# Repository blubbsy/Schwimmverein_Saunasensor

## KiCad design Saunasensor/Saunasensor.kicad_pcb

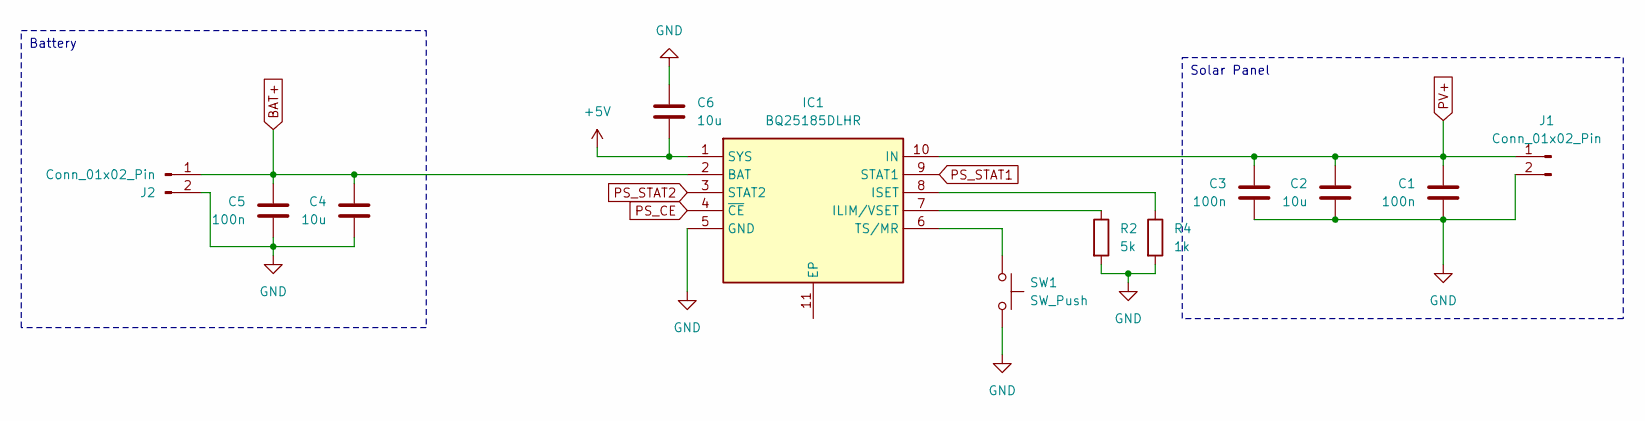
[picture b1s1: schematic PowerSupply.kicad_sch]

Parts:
C1, C3, C5: 100n; C_0805_2012Metric
C2, C4, C6: 10u; C_0805_2012Metric
IC1: BQ25185DLHR; SON40P220X200X80-11N; Mouser Part Number 595-BQ25185DLHR
J1, J2: Conn_01x02_Pin
R2: 5k; R_0805_2012Metric
R4: 1k; R_0805_2012Metric
SW1: SW_Push; SW_Push_1P1T_NO_CK_PTS125Sx43PSMTR

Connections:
+5V: C6.2, IC1.1 (SYS); also elsewhere on the board
BAT+: C4.1, C5.1, IC1.2 (BAT), J2.1; also elsewhere on the board
GND: C1.2, C2.2, C3.2, C4.2, C5.2, C6.1, IC1.5 (GND), J1.2, J2.2, R2.2, R4.2, SW1.2; also elsewhere on the board
unnamed: IC1.7 (ILIM/VSET), R2.1
unnamed: IC1.8 (ISET), R4.1
unnamed: IC1.6 (TS/MR), SW1.1
PS_CE: IC1.4 (~CE); also elsewhere on the board
PS_STAT1: IC1.9 (STAT1); also elsewhere on the board
PS_STAT2: IC1.3 (STAT2); also elsewhere on the board
PV+: C1.1, C2.1, C3.1, IC1.10 (IN), J1.1; also elsewhere on the board

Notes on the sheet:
Solar Panel
Battery

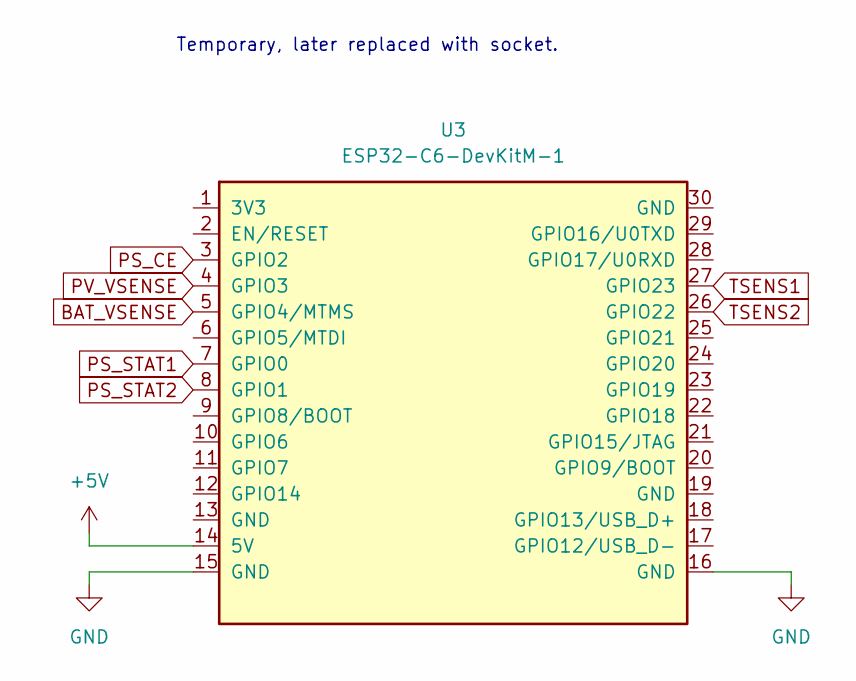
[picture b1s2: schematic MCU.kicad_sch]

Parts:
U3: ESP32-C6-DevKitM-1

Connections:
+5V: U3.14 (5V); also elsewhere on the board
BAT_VSENSE: U3.5 (GPIO4/MTMS); also elsewhere on the board
GND: U3.15 (GND), U3.16 (GND); also elsewhere on the board
PS_CE: U3.3 (GPIO2); also elsewhere on the board
PS_STAT1: U3.7 (GPIO0); also elsewhere on the board
PS_STAT2: U3.8 (GPIO1); also elsewhere on the board
PV_VSENSE: U3.4 (GPIO3); also elsewhere on the board
TSENS1: U3.27 (GPIO23); also elsewhere on the board
TSENS2: U3.26 (GPIO22); also elsewhere on the board

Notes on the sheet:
Temporary, later replaced with socket.

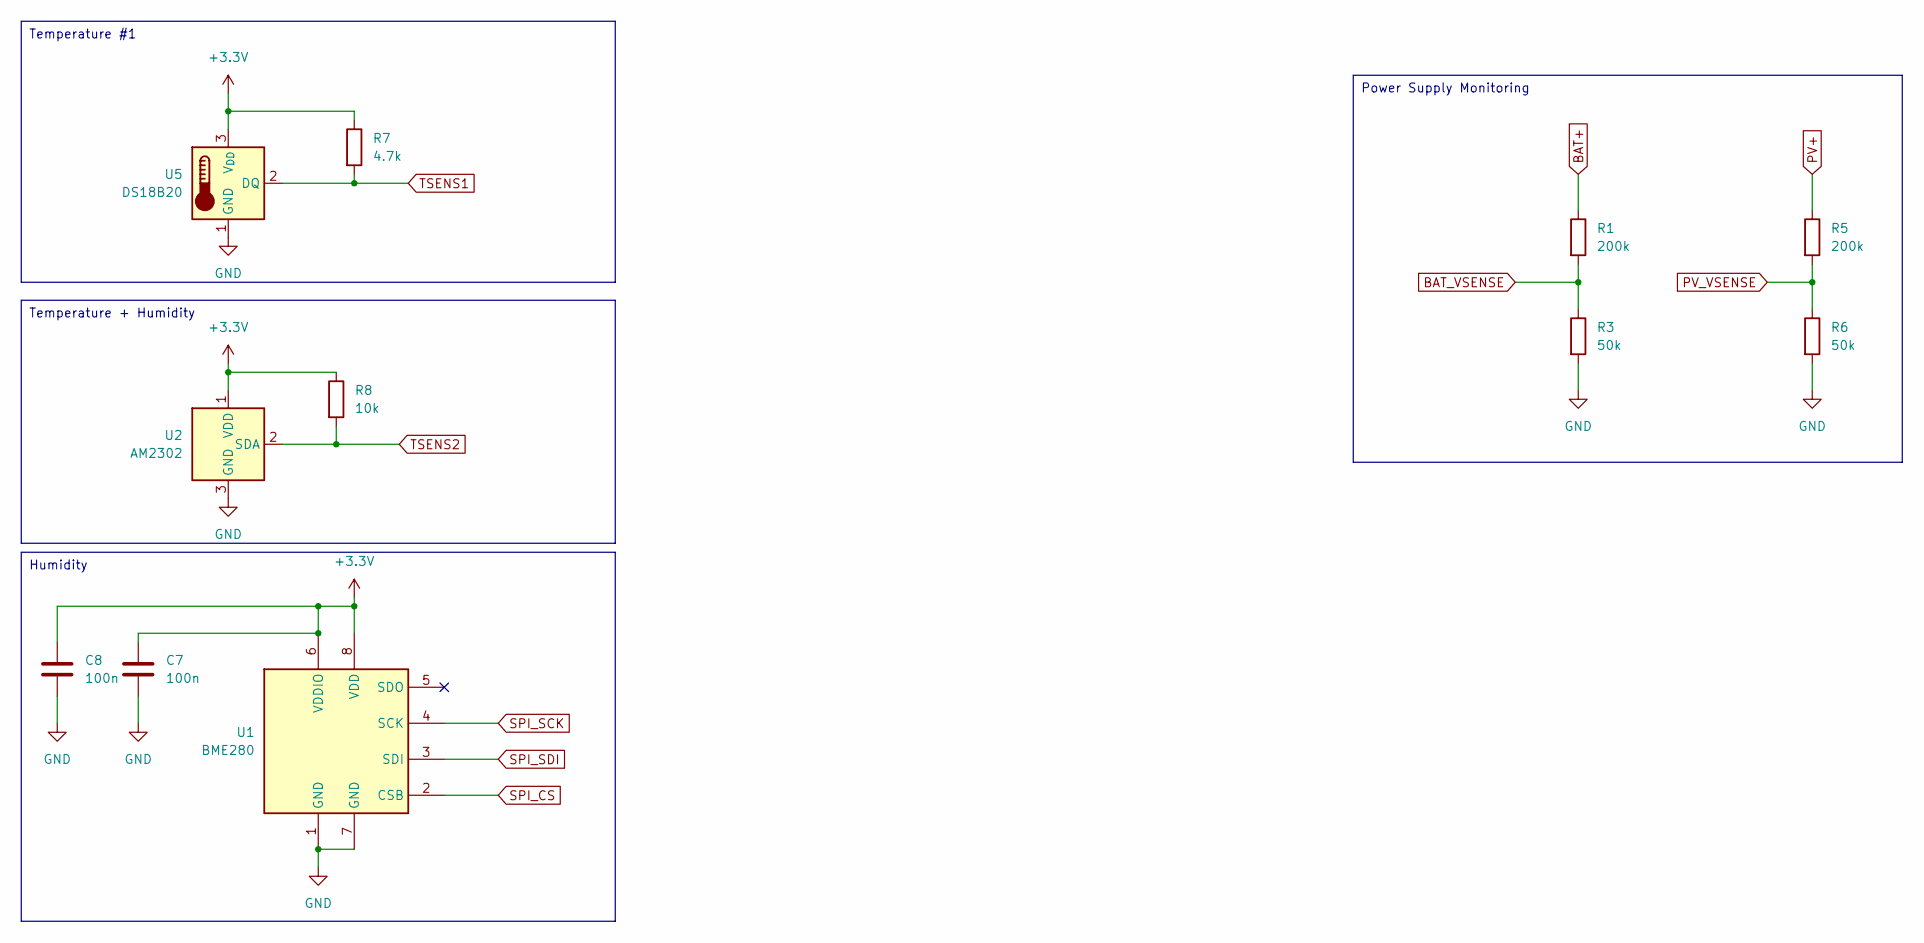
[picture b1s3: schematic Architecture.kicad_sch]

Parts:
C7, C8: 100n; C_0805_2012Metric
R1, R5: 200k; R_0805_2012Metric
R3, R6: 50k; R_0805_2012Metric
R7: 4.7k; R_0805_2012Metric
R8: 10k; R_0805_2012Metric
U1: BME280; Bosch_LGA-8_2.5x2.5mm_P0.65mm_ClockwisePinNumbering
U2: AM2302; ASAIR_AM2302_P2.54mm_Vertical
U5: DS18B20; TO-92_Inline

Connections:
+3.3V: C7.1, C8.1, R7.1, R8.1, U1.6 (VDDIO), U1.8 (VDD), U2.1 (VDD), U5.3 (V_{DD})
BAT+: R1.1; also elsewhere on the board
BAT_VSENSE: R1.2, R3.1; also elsewhere on the board
GND: C7.2, C8.2, R3.2, R6.2, U1.1 (GND), U1.7 (GND), U2.3 (GND), U2.4 (GND), U5.1 (GND); also elsewhere on the board
PV+: R5.1; also elsewhere on the board
PV_VSENSE: R5.2, R6.1; also elsewhere on the board
SPI_CS: U1.2 (CSB)
SPI_SCK: U1.4 (SCK)
SPI_SDI: U1.3 (SDI)
TSENS1: R7.2, U5.2 (DQ); also elsewhere on the board
TSENS2: R8.2, U2.2 (SDA); also elsewhere on the board

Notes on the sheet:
Temperature + Humidity
Humidity
Power Supply Monitoring
Temperature #1

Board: 2 copper layers, 22 parts (0 on the bottom side), 15 nets, no tracks yet.

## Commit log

2025-01-19 started preparing stuff
    started preparing stuff
2025-01-24 Schematic work
    * added sensors
    * added power supply
    * added MCU
2025-01-24 Footprints
    assigned footprints to components
2025-01-24 added gitignore
2025-02-07 cleanup
